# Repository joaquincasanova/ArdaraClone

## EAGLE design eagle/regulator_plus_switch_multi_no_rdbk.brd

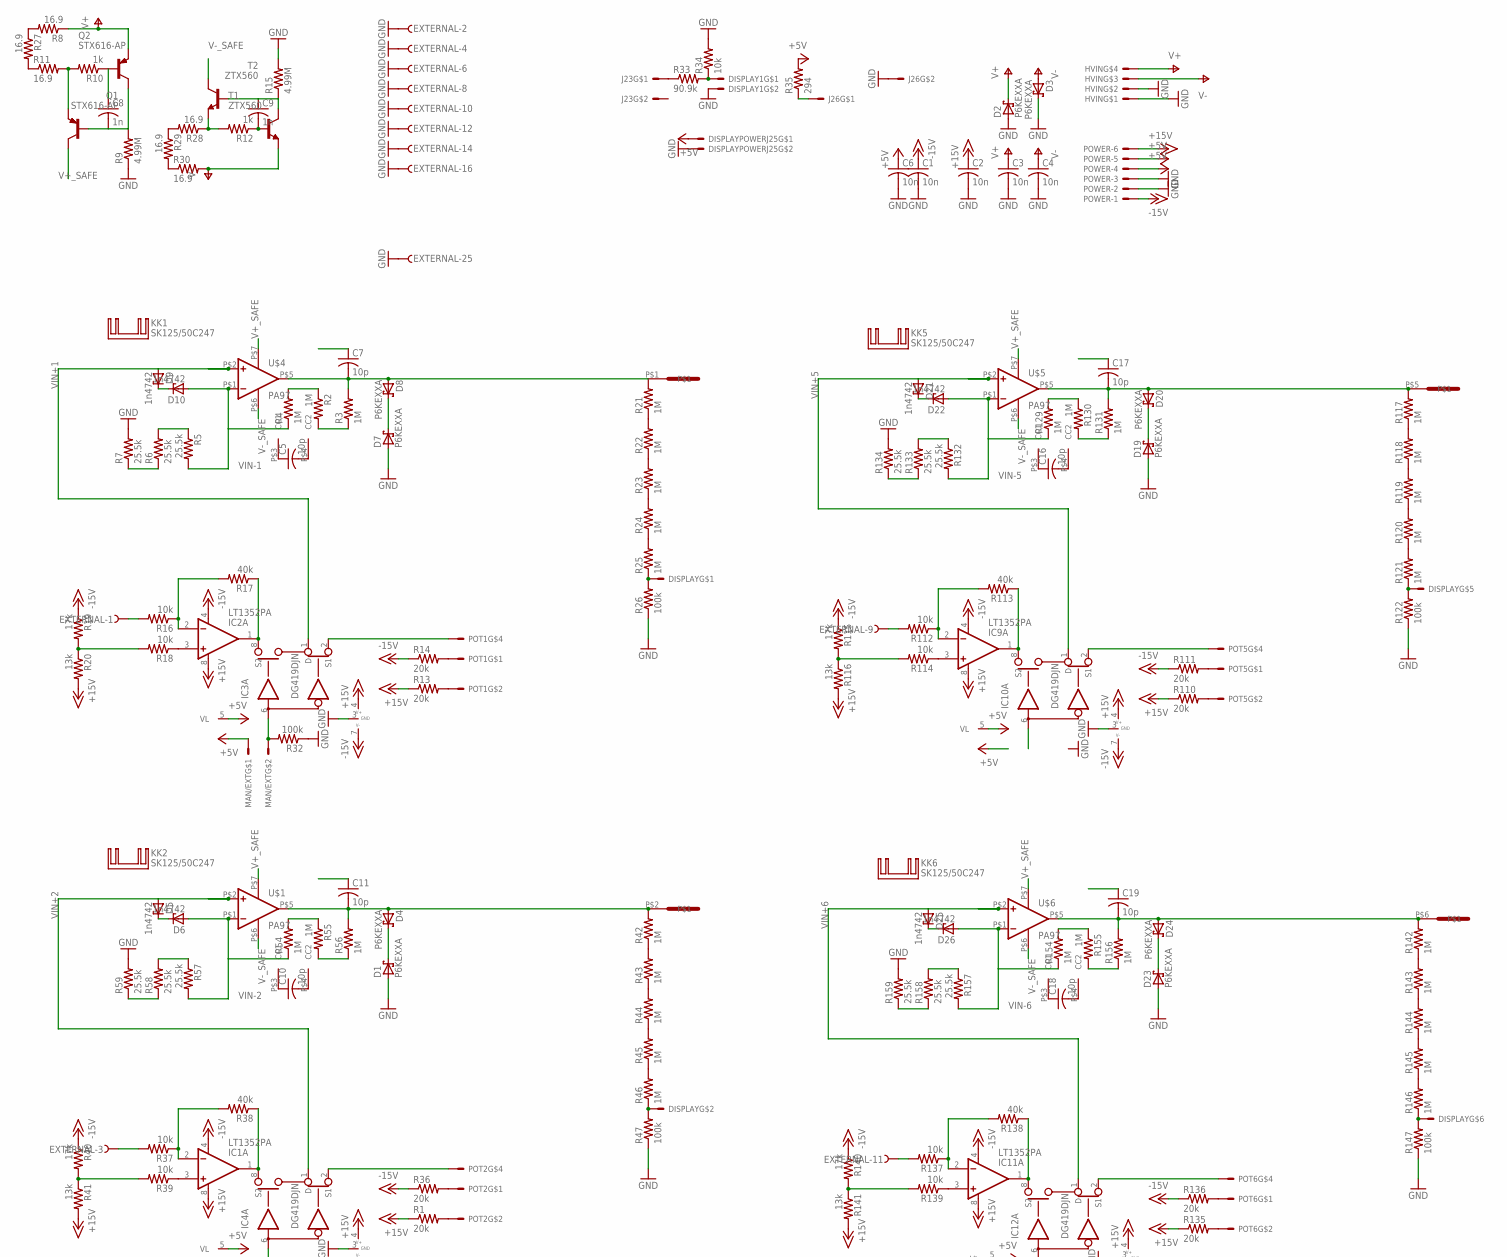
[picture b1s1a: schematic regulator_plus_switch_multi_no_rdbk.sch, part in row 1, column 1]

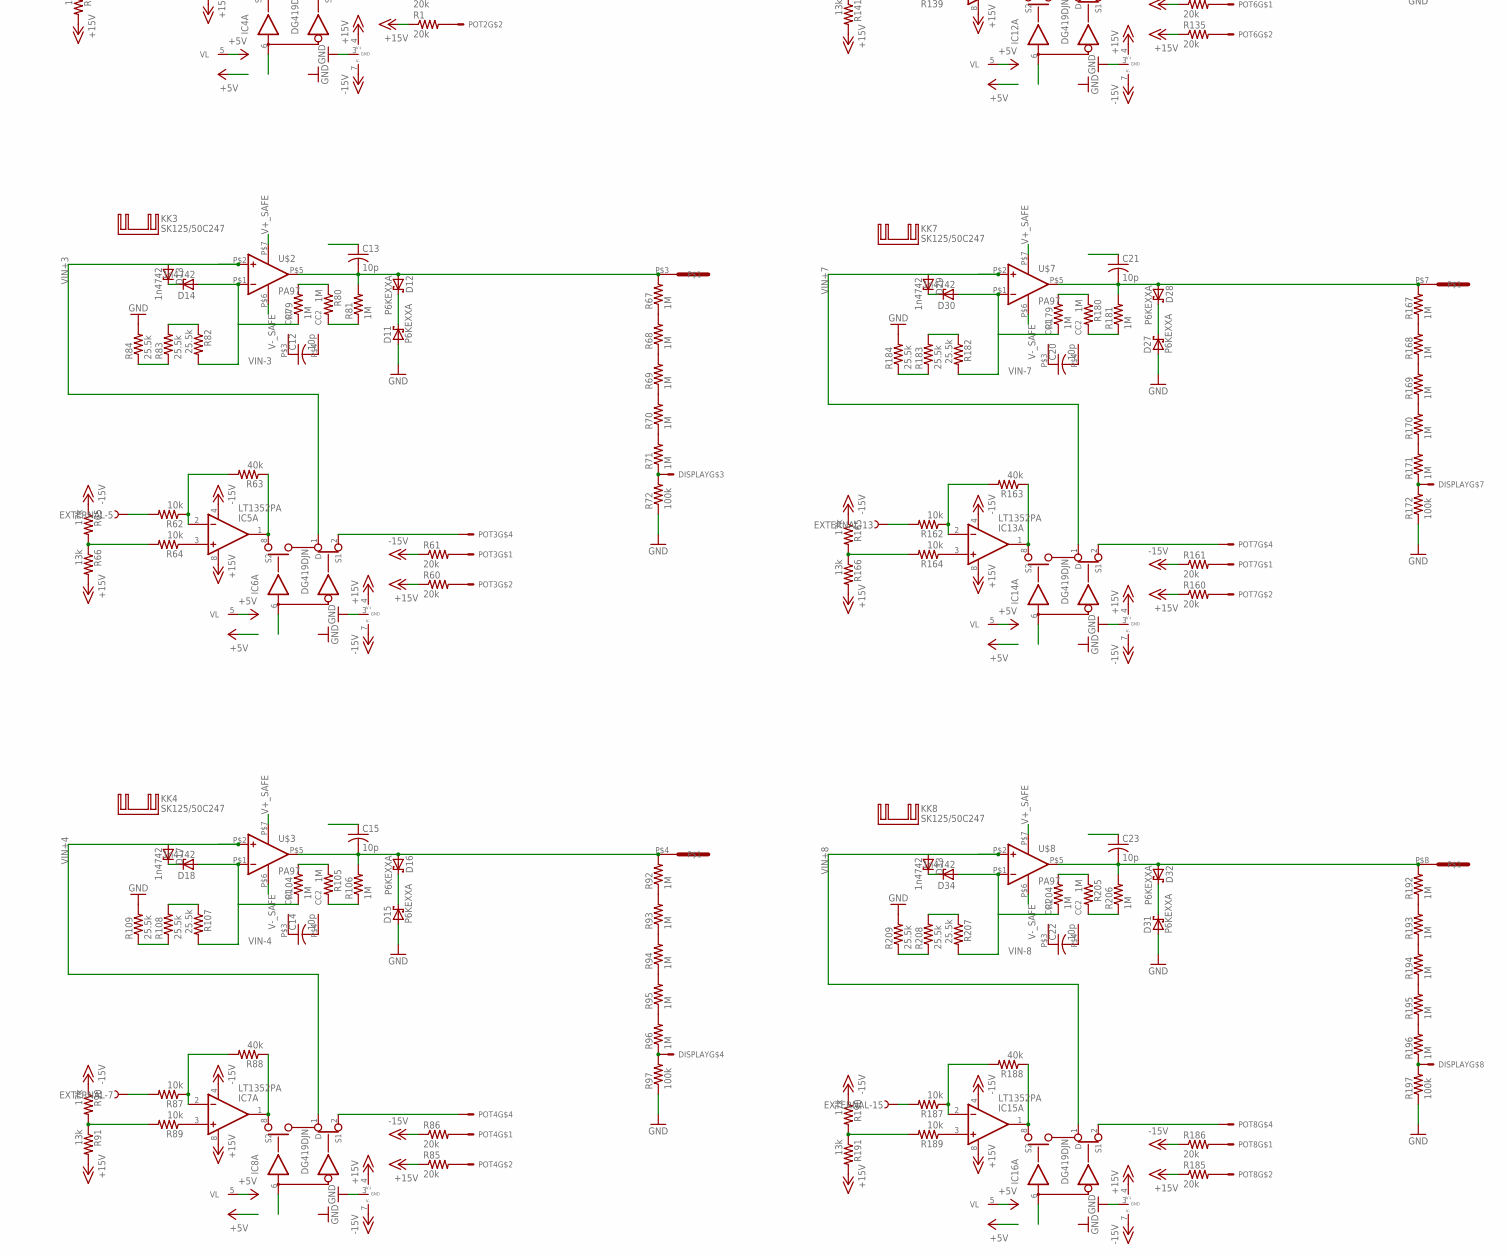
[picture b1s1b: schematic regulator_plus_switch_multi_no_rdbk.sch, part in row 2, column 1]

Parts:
C1, C2, C3, C4, C6: 10n; C075-032X103
C5, C7, C10, C11, C12, C13, C14, C15, C16, C17, C18, C19, C20, C21, C22, C23: 10p; C075-032X103
C8, C9: 1n; C075-032X103
D1, D2, D3, D4, D7, D8, D11, D12, D15, D16, D19, D20, D23, D24, D27, D28, D31, D32: P6KEXXA; C1702-15
D5, D6, D9, D10, D13, D14, D17, D18, D21, D22, D25, D26, D29, D30, D33, D34: 1n4742; DO41Z10
DISPLAY: 5669-8
DISPLAY1: 5569-2
DISPLAYPOWERJ25: 5569-2
EXTERNAL: F25HPS; F25HP
HVIN: 5569-4; 5669-4
IC1, IC2, IC5, IC7, IC9, IC11, IC13, IC15: LT1352PA; DIL08
IC3, IC4, IC6, IC8, IC10, IC12, IC14, IC16: DG419DJN; DIL08
J23, J26: 5569-2
KK1, KK2, KK3, KK4, KK5, KK6, KK7, KK8: SK125/50C247; C247-050
MAN/EXT: 5569-2
OUT: 640584-1
POT1, POT2, POT3, POT4, POT5, POT6, POT7, POT8: 5569-4; 5669-4
POWER: KK-156-6
Q1, Q2: STX616-AP; TO92L
R1, R13, R14, R36, R60, R61, R85, R86, R110, R111, R135, R136, R160, R161, R185, R186: 20k; 0207/10
R2, R3, R4, R21, R22, R23, R24, R25, R42, R43, R44, R45, R46, R54, R55, R56, R67, R68, R69, R70, R71, R79, R80, R81, R92, R93, R94, R95, R96, R104, R105, R106, R117, R118, R119, R120, R121, R129, R130, R131, R142, R143, R144, R145, R146, R154, R155, R156, R167, R168, R169, R170, R171, R179, R180, R181, R192, R193, R194, R195, R196, R204, R205, R206: 1M; 0207/10
R5, R6, R7, R57, R58, R59, R82, R83, R84, R107, R108, R109, R132, R133, R134, R157, R158, R159, R182, R183, R184, R207, R208, R209: 25.5k; 0207/10
R8, R11, R27, R28, R29, R30: 16.9; 0207/10
R9, R15: 4.99M; 0207/10
R10, R12: 1k; 0207/10
R16, R18, R34, R37, R39, R62, R64, R87, R89, R112, R114, R137, R139, R162, R164, R187, R189: 10k; 0207/10
R17, R38, R63, R88, R113, R138, R163, R188: 40k; 0207/10
R19, R40, R65, R90, R115, R140, R165, R190: 17k; 0207/10
R20, R41, R66, R91, R116, R141, R166, R191: 13k; 0207/10
R26, R32, R47, R72, R97, R122, R147, R172, R197: 100k; 0207/10
R33: 90.9k; 0207/10
R35: 294; 0207/10
T1, T2: ZTX560; TO92L
U$1, U$2, U$3, U$4, U$5, U$6, U$7, U$8: PA97; 7SIP

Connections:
+5V: C6.1, DISPLAYPOWERJ25.P$1, IC3.5 (VL), IC4.5 (VL), IC6.5 (VL), IC8.5 (VL), IC10.5 (VL), IC12.5 (VL), IC14.5 (VL), IC16.5 (VL), MAN/EXT.P$1, POWER.4, POWER.5, R35.2
+15V: C2.1, IC1.8 (V+), IC2.8 (V+), IC3.4 (V+), IC4.4 (V+), IC5.8 (V+), IC6.4 (V+), IC7.8 (V+), IC8.4 (V+), IC9.8 (V+), IC10.4 (V+), IC11.8 (V+), IC12.4 (V+), IC13.8 (V+), IC14.4 (V+), IC15.8 (V+), IC16.4 (V+), POWER.6, R1.1, R13.1, R20.2, R41.2, R60.1, R66.2, R85.1, R91.2, R110.1, R116.2, R135.1, R141.2, R160.1, R166.2, R185.1, R191.2
-15V: C1.1, IC1.4 (V-), IC2.4 (V-), IC3.7 (V-), IC4.7 (V-), IC5.4 (V-), IC6.7 (V-), IC7.4 (V-), IC8.7 (V-), IC9.4 (V-), IC10.7 (V-), IC11.4 (V-), IC12.7 (V-), IC13.4 (V-), IC14.7 (V-), IC15.4 (V-), IC16.7 (V-), POWER.1, R14.1, R19.1, R36.1, R40.1, R61.1, R65.1, R86.1, R90.1, R111.1, R115.1, R136.1, R140.1, R161.1, R165.1, R186.1, R190.1
GND: C1.2, C2.2, C3.2, C4.2, C6.2, D1.A, D2.A, D3.C, D7.A, D11.A, D15.A, D19.A, D23.A, D27.A, D31.A, DISPLAY1.P$2, DISPLAYPOWERJ25.P$2, EXTERNAL.2, EXTERNAL.4, EXTERNAL.6, EXTERNAL.8, EXTERNAL.10, EXTERNAL.12, EXTERNAL.14, EXTERNAL.16, EXTERNAL.25, HVIN.P$1, HVIN.P$2, IC3.3 (GND), IC4.3 (GND), IC6.3 (GND), IC8.3 (GND), IC10.3 (GND), IC12.3 (GND), IC14.3 (GND), IC16.3 (GND), J26.P$2, POWER.2, POWER.3, R7.2, R9.1, R15.2, R26.1, R32.1, R34.2, R47.1, R59.2, R72.1, R84.2, R97.1, R109.2, R122.1, R134.2, R147.1, R159.2, R172.1, R184.2, R197.1, R209.2
MAN: IC3.6 (IN), IC4.6 (IN), IC6.6 (IN), IC8.6 (IN), IC10.6 (IN), IC12.6 (IN), IC14.6 (IN), IC16.6 (IN), MAN/EXT.P$2, R32.2
unnamed: R12.2, R28.1, T2.1 (E)
unnamed: C8.1, Q2.2 (B), R10.1
unnamed: C5.1, U$4.P$3 (CC1)
unnamed: C5.2, U$4.P$4 (CC2)
unnamed: Q1.3 (E), R10.2, R11.2
unnamed: IC1.2 (-IN), R37.1, R38.2
unnamed: IC1.3 (+IN), R39.1
unnamed: D7.C, D8.C
unnamed: POT1.P$2, R13.2
unnamed: C8.2, Q1.2 (B), Q2.1 (C), R9.2
unnamed: C7.2, D8.A, OUT.P$1, R3.2, R21.2, U$4.P$5 (OUT)
unnamed: R2.1, R4.2
unnamed: IC3.2 (S1), POT1.P$4
unnamed: R5.1, R6.2
unnamed: POT1.P$1, R14.2
unnamed: R6.1, R7.1
unnamed: C9.2, R12.1, T1.2 (B)
unnamed: R2.2, R3.1
unnamed: C9.1, R15.1, T1.3 (C), T2.2 (B)
unnamed: DISPLAY1.P$1, R33.2, R34.1
unnamed: J23.P$1, R33.1
unnamed: J26.P$1, R35.1
unnamed: R39.2, R40.2, R41.1
unnamed: IC2.2 (-IN), R16.1, R17.2
unnamed: IC2.3 (+IN), R18.1
unnamed: R18.2, R19.2, R20.1
unnamed: IC2.1 (OUT), IC3.8 (S2), R17.1
unnamed: IC1.1 (OUT), IC4.8 (S2), R38.1
unnamed: D9.C, D10.C
unnamed: R21.1, R22.2
unnamed: R22.1, R23.2
unnamed: R23.1, R24.2
unnamed: R24.1, R25.2
unnamed: R8.2, R27.1
unnamed: R11.1, R27.2
unnamed: DISPLAY.P$2, R46.1, R47.2
unnamed: DISPLAY.P$3, R71.1, R72.2
unnamed: R42.1, R43.2
unnamed: DISPLAY.P$4, R96.1, R97.2
unnamed: R43.1, R44.2
unnamed: R44.1, R45.2
unnamed: R45.1, R46.2
unnamed: DISPLAY.P$5, R121.1, R122.2
unnamed: DISPLAY.P$6, R146.1, R147.2
unnamed: DISPLAY.P$7, R171.1, R172.2
unnamed: DISPLAY.P$8, R196.1, R197.2
unnamed: R28.2, R29.1
unnamed: POT2.P$2, R1.2
unnamed: IC4.2 (S1), POT2.P$4
unnamed: POT2.P$1, R36.2
unnamed: C10.1, U$1.P$3 (CC1)
unnamed: C10.2, U$1.P$4 (CC2)
unnamed: C11.2, D4.A, OUT.P$2, R42.2, R56.2, U$1.P$5 (OUT)
unnamed: D1.C, D4.C
unnamed: R54.2, R55.1
unnamed: R57.1, R58.2
unnamed: R58.1, R59.1
unnamed: R55.2, R56.1
unnamed: D5.C, D6.C
unnamed: IC5.2 (-IN), R62.1, R63.2
unnamed: IC5.3 (+IN), R64.1
unnamed: R64.2, R65.2, R66.1
unnamed: IC5.1 (OUT), IC6.8 (S2), R63.1
unnamed: R67.1, R68.2
unnamed: R68.1, R69.2
unnamed: R69.1, R70.2
unnamed: R70.1, R71.2
unnamed: R29.2, R30.1
unnamed: EXTERNAL.1, R16.2
unnamed: EXTERNAL.3, R37.2
unnamed: EXTERNAL.5, R62.2
unnamed: EXTERNAL.7, R87.2
unnamed: POT3.P$2, R60.2
unnamed: IC6.2 (S1), POT3.P$4
unnamed: POT3.P$1, R61.2
unnamed: C12.1, U$2.P$3 (CC1)
unnamed: C12.2, U$2.P$4 (CC2)
unnamed: C13.2, D12.A, OUT.P$3, R67.2, R81.2, U$2.P$5 (OUT)
unnamed: D11.C, D12.C
unnamed: R79.2, R80.1
unnamed: R82.1, R83.2
unnamed: R83.1, R84.1
unnamed: R80.2, R81.1
unnamed: D13.C, D14.C
unnamed: IC7.2 (-IN), R87.1, R88.2
unnamed: IC7.3 (+IN), R89.1
unnamed: R89.2, R90.2, R91.1
unnamed: IC7.1 (OUT), IC8.8 (S2), R88.1
unnamed: R92.1, R93.2
unnamed: R93.1, R94.2
unnamed: R94.1, R95.2
unnamed: R95.1, R96.2
unnamed: EXTERNAL.9, R112.2
unnamed: EXTERNAL.11, R137.2
unnamed: EXTERNAL.13, R162.2
unnamed: EXTERNAL.15, R187.2
unnamed: POT4.P$2, R85.2
unnamed: IC8.2 (S1), POT4.P$4
unnamed: POT4.P$1, R86.2
unnamed: C14.1, U$3.P$3 (CC1)
unnamed: C14.2, U$3.P$4 (CC2)
unnamed: C15.2, D16.A, OUT.P$4, R92.2, R106.2, U$3.P$5 (OUT)
unnamed: D15.C, D16.C
unnamed: R104.2, R105.1
unnamed: R107.1, R108.2
unnamed: R108.1, R109.1
unnamed: R105.2, R106.1
unnamed: D17.C, D18.C
unnamed: IC9.2 (-IN), R112.1, R113.2
unnamed: IC9.3 (+IN), R114.1
unnamed: R114.2, R115.2, R116.1
unnamed: IC9.1 (OUT), IC10.8 (S2), R113.1
unnamed: R117.1, R118.2
unnamed: R118.1, R119.2
unnamed: R119.1, R120.2
unnamed: R120.1, R121.2
unnamed: POT5.P$2, R110.2
unnamed: IC10.2 (S1), POT5.P$4
unnamed: POT5.P$1, R111.2
unnamed: C16.1, U$5.P$3 (CC1)
unnamed: C16.2, U$5.P$4 (CC2)
unnamed: C17.2, D20.A, OUT.P$5, R117.2, R131.2, U$5.P$5 (OUT)
unnamed: D19.C, D20.C
unnamed: R129.2, R130.1
unnamed: R132.1, R133.2
unnamed: R133.1, R134.1
unnamed: R130.2, R131.1
unnamed: D21.C, D22.C
unnamed: IC11.2 (-IN), R137.1, R138.2
unnamed: IC11.3 (+IN), R139.1
unnamed: R139.2, R140.2, R141.1
unnamed: IC11.1 (OUT), IC12.8 (S2), R138.1
unnamed: R142.1, R143.2
unnamed: R143.1, R144.2
unnamed: R144.1, R145.2
unnamed: R145.1, R146.2
unnamed: POT6.P$2, R135.2
unnamed: IC12.2 (S1), POT6.P$4
unnamed: POT6.P$1, R136.2
unnamed: C18.1, U$6.P$3 (CC1)
unnamed: C18.2, U$6.P$4 (CC2)
unnamed: C19.2, D24.A, OUT.P$6, R142.2, R156.2, U$6.P$5 (OUT)
unnamed: D23.C, D24.C
unnamed: R154.2, R155.1
unnamed: R157.1, R158.2
unnamed: R158.1, R159.1
unnamed: R155.2, R156.1
unnamed: D25.C, D26.C
unnamed: IC13.2 (-IN), R162.1, R163.2
unnamed: IC13.3 (+IN), R164.1
unnamed: R164.2, R165.2, R166.1
unnamed: IC13.1 (OUT), IC14.8 (S2), R163.1
unnamed: R167.1, R168.2
unnamed: R168.1, R169.2
unnamed: R169.1, R170.2
unnamed: R170.1, R171.2
unnamed: POT7.P$2, R160.2
unnamed: IC14.2 (S1), POT7.P$4
unnamed: POT7.P$1, R161.2
unnamed: C20.1, U$7.P$3 (CC1)
unnamed: C20.2, U$7.P$4 (CC2)
unnamed: C21.2, D28.A, OUT.P$7, R167.2, R181.2, U$7.P$5 (OUT)
unnamed: D27.C, D28.C
unnamed: R179.2, R180.1
unnamed: R182.1, R183.2
unnamed: R183.1, R184.1
unnamed: R180.2, R181.1
unnamed: D29.C, D30.C
unnamed: IC15.2 (-IN), R187.1, R188.2
unnamed: IC15.3 (+IN), R189.1
unnamed: R189.2, R190.2, R191.1
unnamed: IC15.1 (OUT), IC16.8 (S2), R188.1
unnamed: R192.1, R193.2
unnamed: R193.1, R194.2
unnamed: R194.1, R195.2
unnamed: R195.1, R196.2
unnamed: POT8.P$2, R185.2
unnamed: IC16.2 (S1), POT8.P$4
unnamed: POT8.P$1, R186.2
unnamed: C22.1, U$8.P$3 (CC1)
unnamed: C22.2, U$8.P$4 (CC2)
unnamed: C23.2, D32.A, OUT.P$8, R192.2, R206.2, U$8.P$5 (OUT)
unnamed: D31.C, D32.C
unnamed: R204.2, R205.1
unnamed: R207.1, R208.2
unnamed: R208.1, R209.1
unnamed: R205.2, R206.1
unnamed: D33.C, D34.C
unnamed: DISPLAY.P$1, R25.1, R26.2
V+: C3.1, D2.C, HVIN.P$4, Q2.3 (E), R8.1
V+_SAFE: Q1.1 (C), U$1.P$7 (V+), U$2.P$7 (V+), U$3.P$7 (V+), U$4.P$7 (V+), U$5.P$7 (V+), U$6.P$7 (V+), U$7.P$7 (V+), U$8.P$7 (V+)
V-: C4.1, D3.A, HVIN.P$3, R30.2, T1.1 (E)
V-_SAFE: T2.3 (C), U$1.P$6 (V-), U$2.P$6 (V-), U$3.P$6 (V-), U$4.P$6 (V-), U$5.P$6 (V-), U$6.P$6 (V-), U$7.P$6 (V-), U$8.P$6 (V-)
VIN+1: D9.A, IC3.1 (D), U$4.P$2 (+IN)
VIN+2: D5.A, IC4.1 (D), U$1.P$2 (+IN)
VIN+3: D13.A, IC6.1 (D), U$2.P$2 (+IN)
VIN+4: D17.A, IC8.1 (D), U$3.P$2 (+IN)
VIN+5: D21.A, IC10.1 (D), U$5.P$2 (+IN)
VIN+6: D25.A, IC12.1 (D), U$6.P$2 (+IN)
VIN+7: D29.A, IC14.1 (D), U$7.P$2 (+IN)
VIN+8: D33.A, IC16.1 (D), U$8.P$2 (+IN)
VIN-1: C7.1, D10.A, R4.1, R5.2, U$4.P$1 (-IN)
VIN-2: C11.1, D6.A, R54.1, R57.2, U$1.P$1 (-IN)
VIN-3: C13.1, D14.A, R79.1, R82.2, U$2.P$1 (-IN)
VIN-4: C15.1, D18.A, R104.1, R107.2, U$3.P$1 (-IN)
VIN-5: C17.1, D22.A, R129.1, R132.2, U$5.P$1 (-IN)
VIN-6: C19.1, D26.A, R154.1, R157.2, U$6.P$1 (-IN)
VIN-7: C21.1, D30.A, R179.1, R182.2, U$7.P$1 (-IN)
VIN-8: C23.1, D34.A, R204.1, R207.2, U$8.P$1 (-IN)

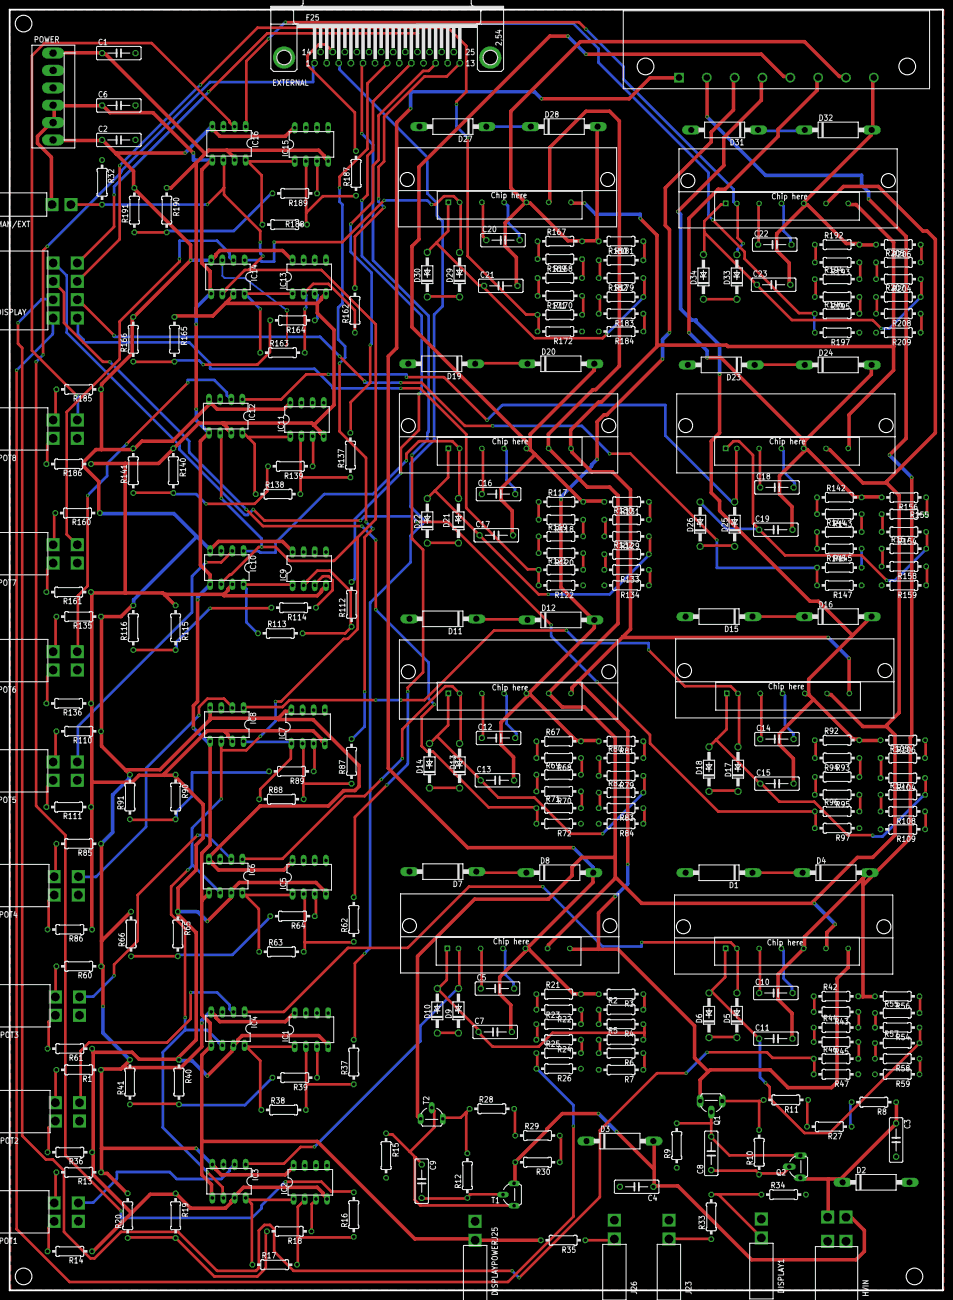
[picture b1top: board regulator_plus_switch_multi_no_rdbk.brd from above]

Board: 2 copper layers, 212.9 x 292.1 mm, 277 parts (0 on the bottom side), 214 nets.

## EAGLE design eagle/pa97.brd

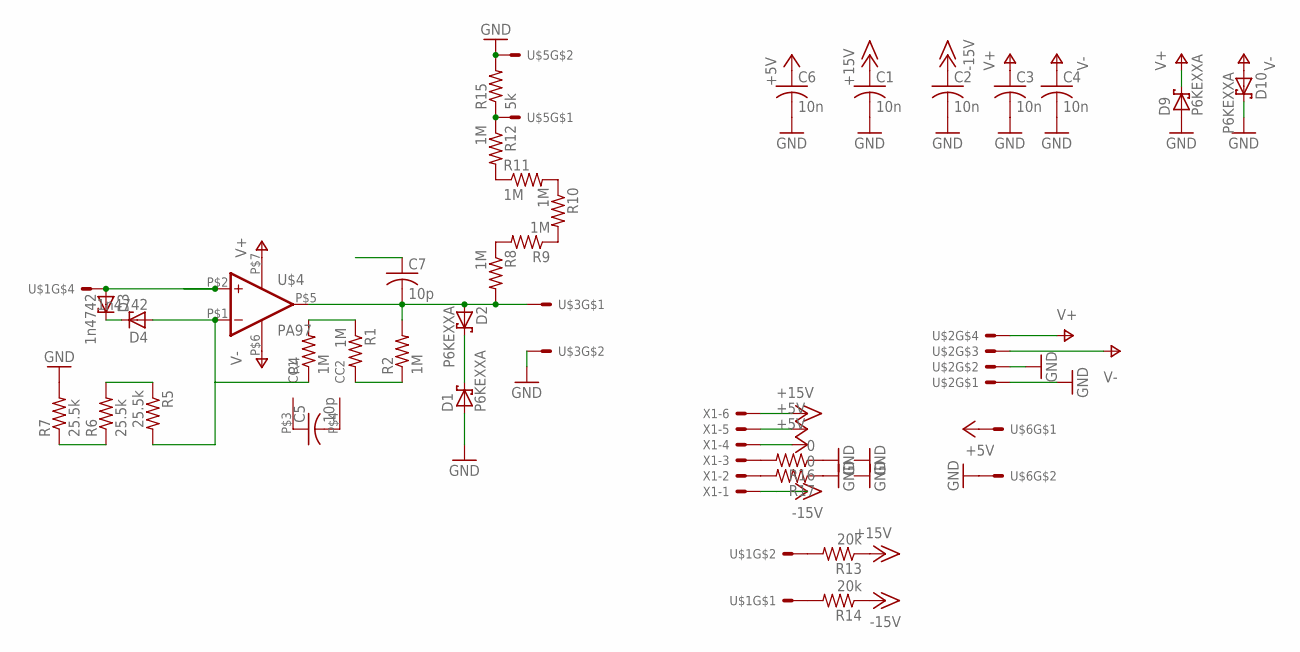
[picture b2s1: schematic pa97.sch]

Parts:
C1, C2, C3, C4, C6: 10n; C075-032X103
C5, C7: 10p; C075-032X103
D1, D2, D9, D10: P6KEXXA; C1702-15
D3, D4: 1n4742; DO41Z10
R1, R2, R4, R8, R9, R10, R11, R12: 1M; 0207/10
R5, R6, R7: 25.5k; 0207/10
R13, R14: 20k; 0207/10
R15: 5k; 0207/10
R16, R17: 0; 0207/10
U$1, U$2: 5569-4; 5669-4
U$3, U$5, U$6: 5569-2
U$4: PA97; 7SIP
X1: KK-156-6

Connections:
+5V: C6.1, U$6.P$1, X1.4, X1.5
+15V: C1.1, R13.1, X1.6
-15V: C2.1, R14.1, X1.1
GND: C1.2, C2.2, C3.2, C4.2, C6.2, D1.A, D9.A, D10.C, R7.2, R15.2, R16.1, R17.1, U$2.P$1, U$2.P$2, U$3.P$2, U$5.P$2, U$6.P$2
unnamed: D1.C, D2.C
unnamed: R1.1, R4.2
unnamed: D4.A, R4.1, R5.2, U$4.P$1 (-IN)
unnamed: R5.1, R6.2
unnamed: R6.1, R7.1
unnamed: C5.1, U$4.P$3 (CC1)
unnamed: C5.2, U$4.P$4 (CC2)
unnamed: R1.2, R2.1
unnamed: R13.2, U$1.P$2
unnamed: C7.2, D2.A, R2.2, R8.2, U$3.P$1, U$4.P$5 (OUT)
unnamed: R8.1, R9.2
unnamed: D3.A, U$1.P$4, U$4.P$2 (+IN)
unnamed: R9.1, R10.2
unnamed: R10.1, R11.2
unnamed: R11.1, R12.2
unnamed: R12.1, R15.1, U$5.P$1
unnamed: R16.2, X1.3
unnamed: R17.2, X1.2
unnamed: D3.C, D4.C
unnamed: R14.2, U$1.P$1
V+: C3.1, D9.C, U$2.P$4, U$4.P$7 (V+)
V-: C4.1, D10.A, U$2.P$3, U$4.P$6 (V-)

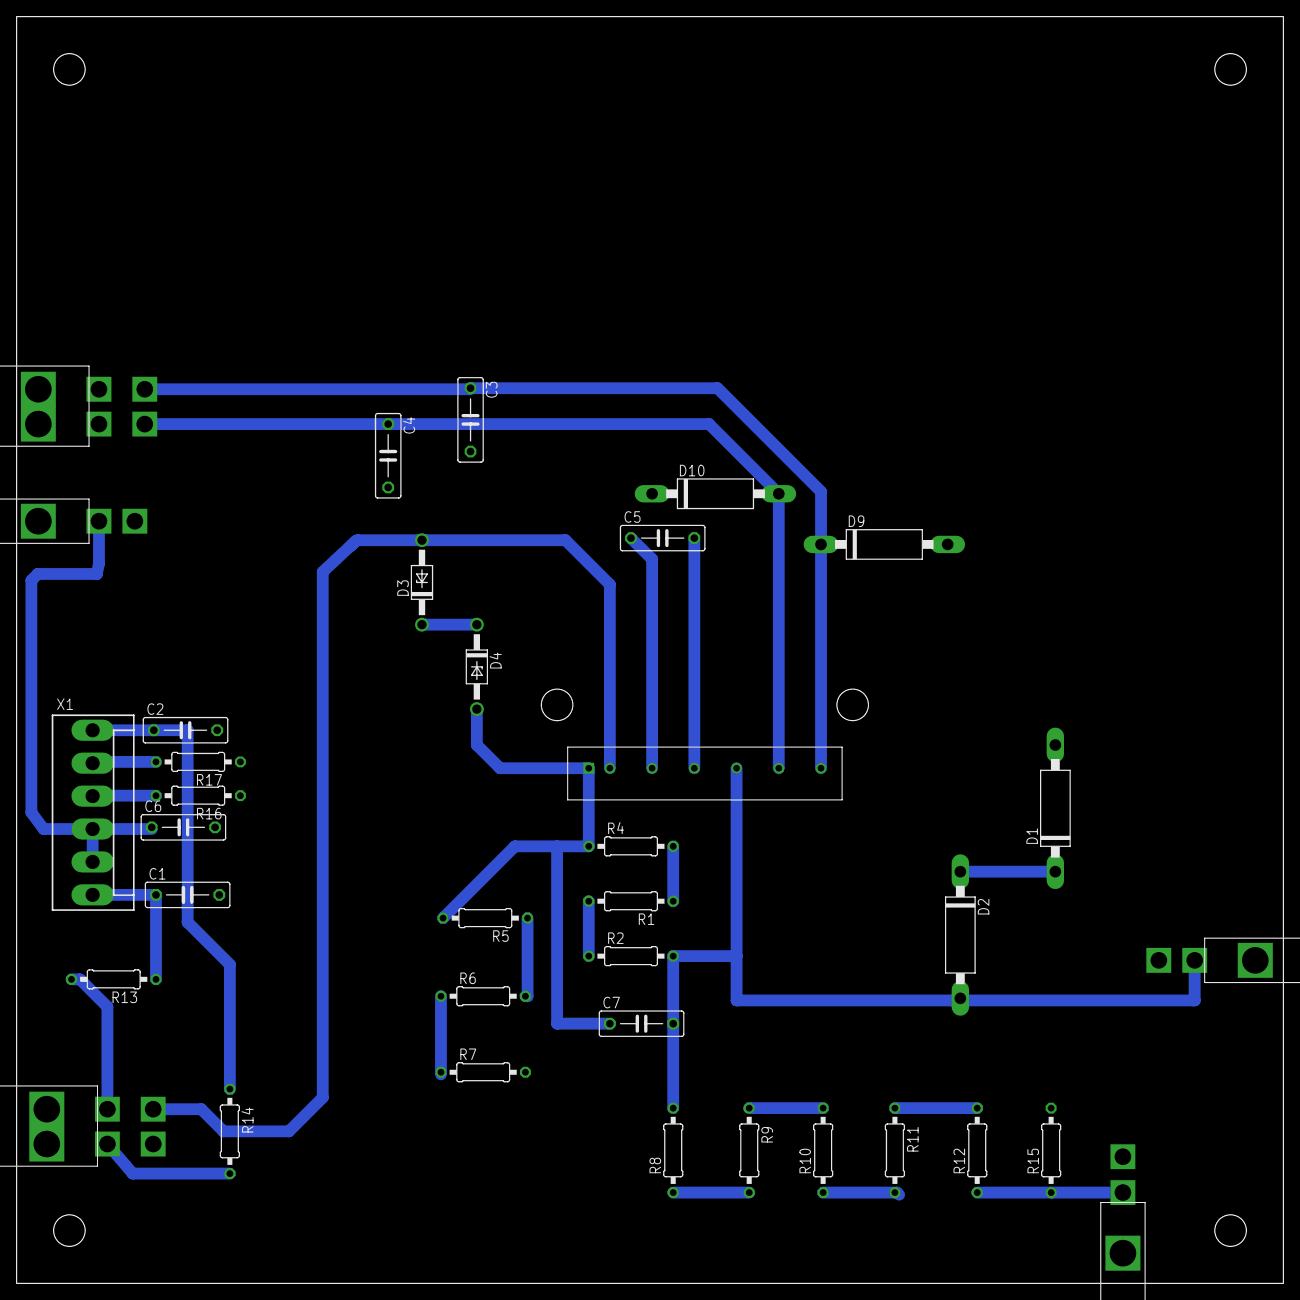
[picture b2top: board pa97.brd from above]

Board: 2 copper layers, 152.4 x 152.4 mm, 36 parts (0 on the bottom side), 26 nets.

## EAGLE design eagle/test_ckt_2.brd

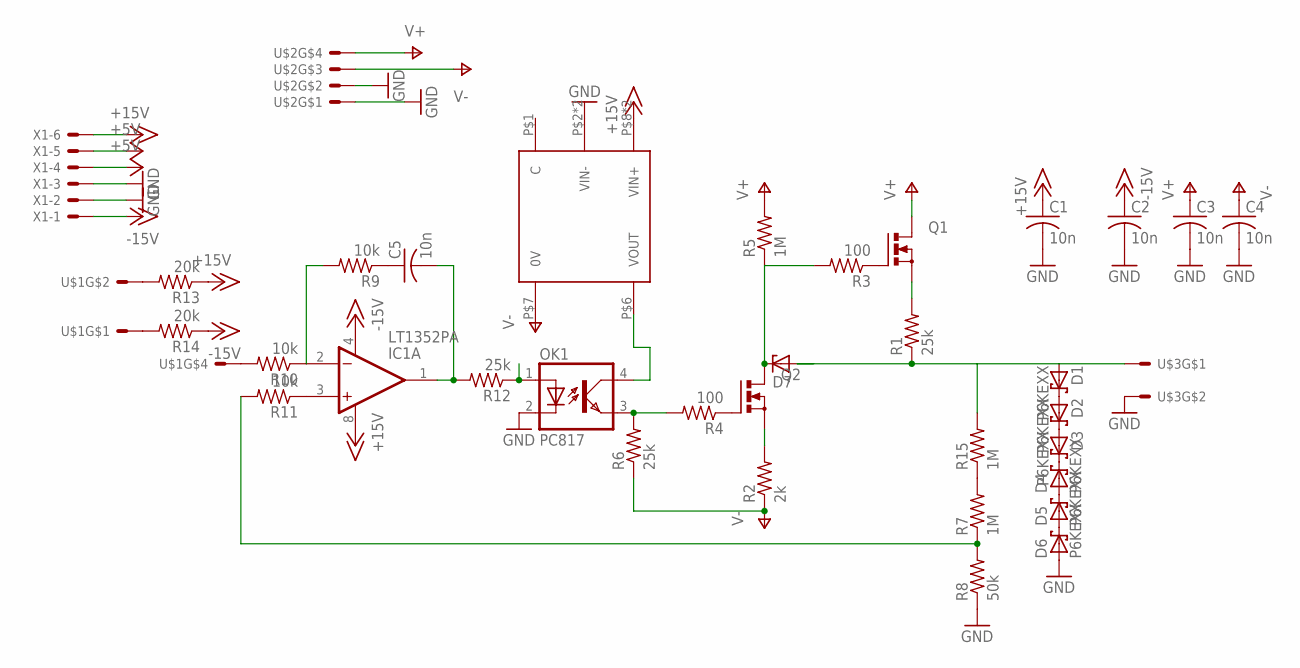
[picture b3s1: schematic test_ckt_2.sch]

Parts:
C1, C2, C3, C4, C5: 10n; C075-032X103
D1, D2, D3, D4, D5, D6: P6KEXX; CB417-15
D7: ZENER-DIODEZD-12.5; ZDIO12.5
DC1: NCS
IC1: LT1352PA; DIL08
OK1: PC817; DIL04
Q1, Q2: PMOSFET_NTO220BV; TO220BV
R1, R6: 25k; 0207/10
R2: 2k; 0207/10
R3, R4: 100; 0207/10
R5, R7, R15: 1M; 0414/15
R8: 50k; 0207/10
R9, R10, R11: 10k; 0207/10
R12: 25k; 0207/15
R13, R14: 20k; 0207/10
U$1, U$2: 5569-4; 5669-4
U$3: 5569-2
X1: KK-156-6

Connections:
+5V: X1.4, X1.5
+15V: C1.1, DC1.P$8 (VIN+), DC1.P$9 (VIN+), IC1.8 (V+), R13.1, X1.6
-15V: C2.1, IC1.4 (V-), R14.1, X1.1
GND: C1.2, C2.2, C3.2, C4.2, D6.A, DC1.P$2 (VIN-), DC1.P$3 (VIN-), OK1.2 (C), R8.1, U$2.P$1, U$2.P$2, U$3.P$2, X1.2, X1.3
unnamed: D1.C, D2.A
unnamed: D2.C, D3.A
unnamed: D3.C, D4.C
unnamed: D4.A, D5.C
unnamed: D5.A, D6.C
unnamed: Q1.G, R3.1
unnamed: D7.C, Q2.D, R3.2, R5.1
unnamed: Q1.S, R1.2
unnamed: R13.2, U$1.P$2
unnamed: D1.A, D7.A, R1.1, R15.2, U$3.P$1
unnamed: Q2.G, R4.1
unnamed: OK1.3 (EMIT), R4.2, R6.2
unnamed: R10.2, U$1.P$4
unnamed: Q2.S, R2.2
unnamed: DC1.P$6 (VOUT), OK1.4 (COL)
unnamed: C5.1, R9.1
unnamed: IC1.2 (-IN), R9.2, R10.1
unnamed: C5.2, IC1.1 (OUT), R12.2
unnamed: IC1.3 (+IN), R11.1
unnamed: R7.1, R8.2, R11.2
unnamed: R7.2, R15.1
unnamed: R14.2, U$1.P$1
unnamed: OK1.1 (A), R12.1
V+: C3.1, Q1.D, R5.2, U$2.P$4
V-: C4.1, DC1.P$7 (0V), R2.1, R6.1, U$2.P$3

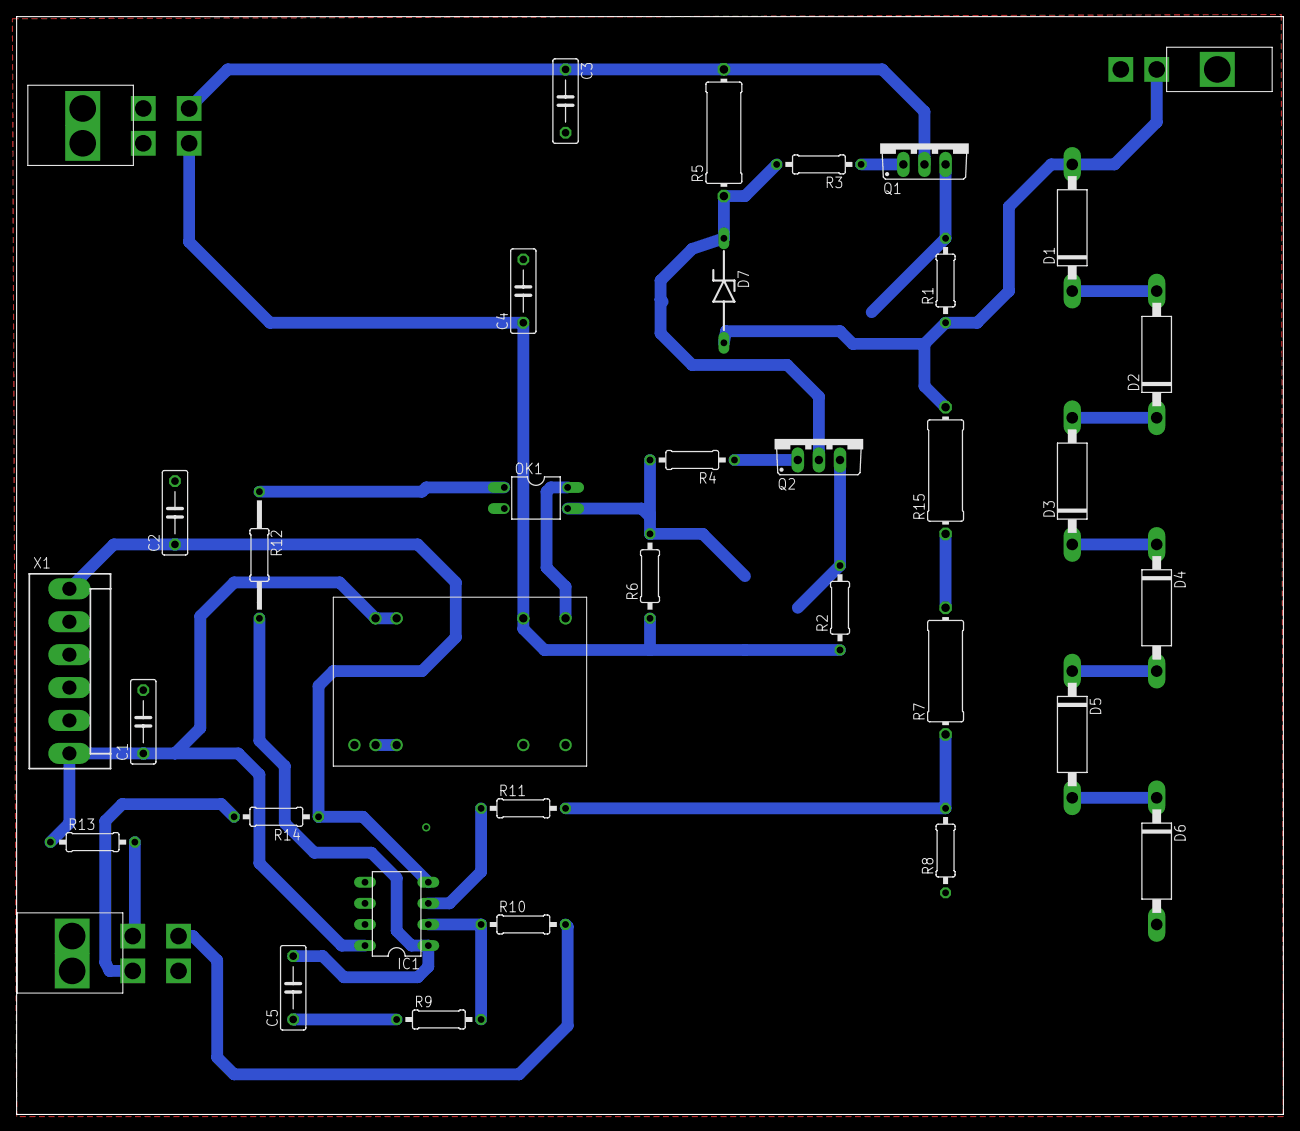
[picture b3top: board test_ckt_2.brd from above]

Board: 2 copper layers, 152.4 x 132.1 mm, 36 parts (0 on the bottom side), 29 nets.

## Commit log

2015-12-22 :neckbeard: Added .gitattributes & .gitignore files
2015-12-22 Clone of aradara regulator - 8 channel supply
2015-12-22 Fix pin assignment minifit Jr
2016-01-06 More fixes...and a board with digital in
2016-01-08 multi-channel
2016-01-13 "Works" but not full scale yet
2016-01-22 Solution to full scale?
2016-02-03 Ardara clone fixes question mark
    vegemite
2016-02-24 pa 97 circuit
2016-02-24 add display out
2016-02-29 pa97 test board
2016-03-18 Test layouts pa97
2016-03-23 regulator
2016-03-25 overcurrent, worked out connectors
2016-03-27 yay led switch worked out
2016-03-29 big board
2016-03-31 8chan
2016-04-08 submit 8 chan
2016-04-26 fix multichannel bugs
2016-05-18 all good
